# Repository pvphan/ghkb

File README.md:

# mGH60

a 'mini' clone of the [GH60](www.github.com/komar007/ghkb) by @komar007. 

its purpose is to be used for the inexpensive development of keyboard prototypes

currently at revision 'a', shared on [OSHPark](https://oshpark.com/shared_projects/XVIElYy4) ($16.50 for 3 PCB, BOM cost ~$9 for 1x on DigiKey).

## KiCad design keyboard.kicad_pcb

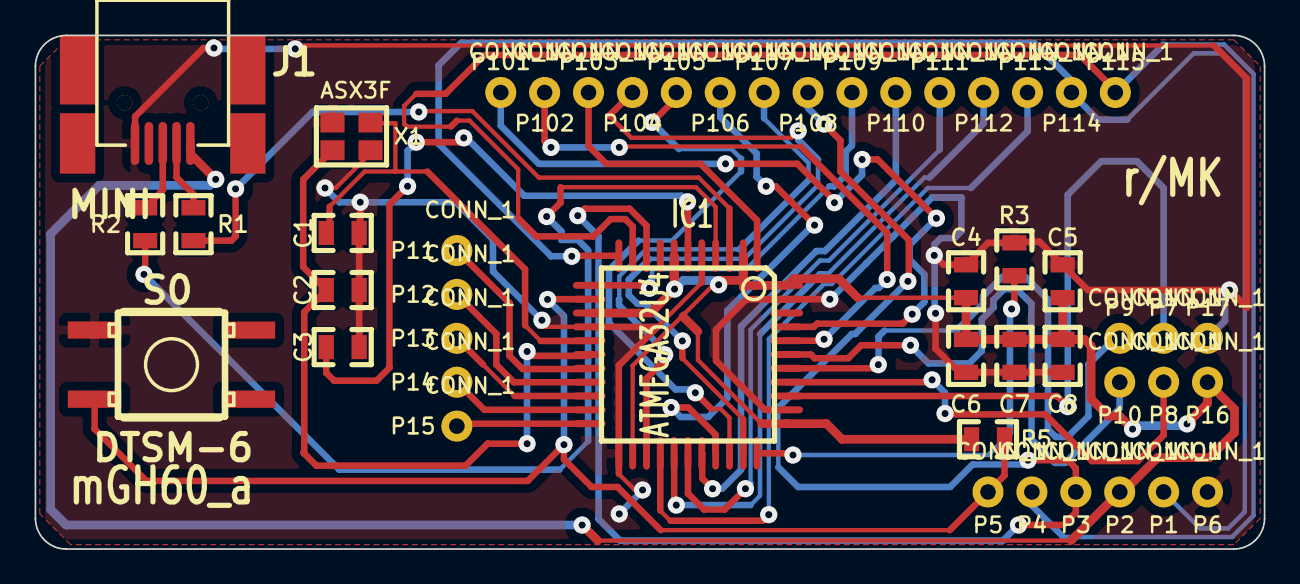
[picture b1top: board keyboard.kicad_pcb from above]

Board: 2 copper layers, 71.1 x 29.7 mm, 48 parts (0 on the bottom side), 35 nets.

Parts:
C1, C2: 22p; SM0805
C3, C8: 1u; SM0805
C4, C5, C6, C7: 100n; SM0805
IC1: ATMEGA32U4; TQFP44
J1: MINI; 67503
P1, P2, P3, P4, P5, P6, P7, P8, P9, P10, P11, P12, P13, P14, P15, P16, P17, P101, P102, P103, P104, P105, P106, P107, P108, P109, P110, P111, P112, P113, P114, P115: CONN_1; pad
R1, R2: 22; SM0805
R3, R5: 10k; SM0805
S0: DTSM-6; KSEM31GLFS
X1: ASX3F

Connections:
/GPIO0: IC1.36, P7.1
/GPIO1: IC1.37, P8.1
/GPIO2: IC1.38, P9.1
/GPIO3: IC1.39, P10.1
/MISO: IC1.11, P1.1, P114.1
/MOSI: IC1.10, P4.1, P115.1
/SCK: IC1.9, P3.1, P108.1
/col1: IC1.41, P101.1
/col2: IC1.40, P102.1
/col3: IC1.1, P103.1
/col4: IC1.32, P104.1
/col5: IC1.31, P105.1
/col6: IC1.30, P106.1
/col7: IC1.25, P107.1
/col9: IC1.12, P109.1
/col10: IC1.29, P110.1
/col11: IC1.28, P111.1
/col12: IC1.27, P112.1
/col13: IC1.26, P113.1
/row1: IC1.18, P11.1
/row2: IC1.19, P12.1
/row3: IC1.20, P13.1
/row4: IC1.21, P14.1
/row5: IC1.22, P15.1
/~RES~: IC1.13, P5.1, R5.2, S0.3
GND: C1.2, C2.2, C3.2, C4.2, C5.2, C6.2, C7.2, C8.2, IC1.5, IC1.15, IC1.23, IC1.35, IC1.43, J1.5, P6.1, P17.1, R3.2, S0.1, X1.2, X1.4
unnamed: J1.2, R1.2
unnamed: J1.3, R2.2
unnamed: IC1.33, R3.1
unnamed: C1.1, IC1.16, X1.1
unnamed: C2.1, IC1.17, X1.3
unnamed: C3.1, IC1.6
unnamed: IC1.4, R2.1
unnamed: IC1.3, R1.1
VCC: C4.1, C5.1, C6.1, C7.1, C8.1, IC1.2, IC1.7, IC1.14, IC1.24, IC1.34, IC1.44, J1.1, P2.1, P16.1, R5.1

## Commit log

2016-01-10 converted to mGH60_a debugger
2017-03-25 adding uart demo for ble113
2017-03-25 added all(?) relevant files from BLE113 SDK (v 1.5)
2017-04-03 added bin/ for ble113
2017-04-03 adding testapp (WIP) folder
2017-04-03 modified gatt profiles for testapp (syntax-only changes to keyboard example)
2017-04-03 trying to match up some of the gatt and project parameters to make BLE113 discoverable
